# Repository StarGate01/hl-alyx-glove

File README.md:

# Half-Life: Alyx Gravity Glove Replica
Firmware, Hardware and Models for a [Half-Life: Alyx](https://store.steampowered.com/app/546560/HalfLife_Alyx/) inspired glove cosplay prop. Based around an ATMega328p / Arduino Uno.

Also check out the [other images](https://github.com/StarGate01/hl-alyx-glove/tree/master/images)!

## Features

 - Detailed replica of the secondary-hand glove
   - Based on in-game 3D models
 - Custom printed circuit board
   - Small and compact due to SMD design
   - Three red LED matrices for hearts
   - Two individually controllable green status LEDs
   - Two orange finger attractor LEDs
   - Blue 128x64 pixel OLED screen for resin count
   - Red check engine LED light 
   - Moveable attractor fingers
 - Uses standard components for power source and control
 - Microcontroller can be easily reprogrammed
 - Cosmetic parts are printable on any standard 3D printer

## State of the Project

<details>
  <summary>PCB Revision 1: Proof of concept - Completed</summary>

  - [x] OLED rendering of resin count and sprite
  - [x] Display animations on 3 LED matrices
  - [x] Drive 2 green status LEDs
  - [x] Drive check engine LED
  - [x] Evaluate barebone IC
  - [x] Evaluate display drivers
  - [x] Manufacture board
  - [x] Validate board

</details>
 
<details>
  <summary>PCB Revision 2: Refinement - Completed</summary>

  - [x] Add buttons
  - [x] Add 0.1uF caps to driver ICs
  - [x] Larger power traces
  - [x] Re-think trace width in general
  - [x] Properly lay out mounting holes
  - [x] Optimize VCC trace
  - [x] Move OLED connector
  - [x] Optimize board size
  - [x] Think about inertial measurement unit
  - [x] Drive decorative yellow LEDs
  - [x] Improve ground plane stitching
  - [x] Add source info to silkscreen
  - [x] Add component orientation to  silkscreen
  - [x] Evaluate acceleration sensor
  - [x] Manufacture board
  - [x] Validate board

</details>

<details>
  <summary>Firmware Revision 1: Tests - Completed</summary>

  - [x] Test sensor
  - [x] Display resin count
  - [x] Display blinking hearts
  - [x] Flash LEDs
  - [x] Read buttons

</details>

<details>
  <summary>Firmware Revision 2: Demo mode - Completed</summary>

  - [x] State management w/ buttons
  - [x] LED control
  - [x] Adjustable amount of hearts and resin

</details>

<details>
  <summary>Firmware Revision 3: Proper functionality - In Progress</summary>

  - [ ] Wrist flick detection

</details>

<details>
  <summary>Power System - Completed</summary>

  - [x] Battery selection
  - [x] Charging management
  - [x] Verify power system

</details>

<details>
  <summary>CAD and 3D-Printing - Completed</summary>

  - [x] Acquire gloves
  - [x] Export models from game
  - [x] Design decorative parts
  - [x] Adapt decorative parts to 3D-Printing
  - [x] Think about paint and mounting
  - [x] Design battery holder
  - [x] Design PCB mount
  - [x] Mount to glove

</details>

<details>
  <summary>Final Assembly - Completed</summary>

  - [x] Proper paintjob
  - [x] Paint copper elements and add wires
  - [x] LED mounting

</details>

## Software

Clone this repository using `git clone` and open it up in the [PlatformIO IDE](https://platformio.org/).

Edit `include/hardware_config.h` if your pin layout differs.

Finally, use PlatformIO to compile and upload the program. A debug configuration for the Arduino Uno (`uno`) and a release configuration for the PCB (`barebone`) are available. To program the barebone chip, you need a ISP programmer such as a AVRISP, USBasp or Arduino as ISP.

### Compiling Modified Sprites

Use GIMP to export the `xcf` image files into `xdm` files. Make sure to declare the buffers as `PROGMEM`.

### Compiling Modified Fonts

Use a tool like `bdfedit` to view or edit the font.

Install `bdfresize` from your package manager.

Clone [olikraus/u8g2](https://github.com/olikraus/u8g2) and change into the `tools/font/bdfconv` directory. Run `make` and copy or link the `bdfconv` executable to somewhere you can run it.

Change into the `res` directory of this repository. Then run `./font.sh` to pre-compile the font.

## Software Components

 - Arduino
   - [Arduino Framework](https://www.arduino.cc/)
 - 8x8 mini 1.9mm LED matrix with MAX7219 IC using software SPI
   - [wayoda/LedControl](https://platformio.org/lib/show/914/LedControl)
 - 128x64 1.3 inch OLED using hardware I2C
   - [olikraus/U8g2](https://platformio.org/lib/show/942/U8g2)
 - GY-61 ADXL335 Breakout
   - Analog input

## Electronics

Most parts are pretty standard, eg. THT resistors, capacitors and LEDs. Pretty much any electronics store should carry them.

The main controller is a ATMega328p, the same as the Arduino Uno uses. These ICs are cheap for what they offer and also available pretty much everywhere.

The 1.9mm LED matrices are a special part, because they are the "mini" version of the much more widely used 3.0mm/3.75mm 8x8 LED matrices. I bought them from [AliExpress](https://de.aliexpress.com/item/4000931195417.html). The OLED is a fairly standard "Arduino-type" breakout board, and commonly available in blue, yellow and white. [Amazon](https://www.amazon.com/gp/product/B07D9G11DZ) carries them, and so does [AliExpress](https://de.aliexpress.com/item/1005001355009919.html). 

The surface mount LED is a 5050 SMT LED, which is also commonly used in LED strips and can be found at many stores, for example at [Ebay](https://www.ebay.com/itm/LED-Light-SMD-SMT-0603-0805-1206-7030-3020-5730-5050-3528-335-Super-bright/302940504403).

The display drivers are MAX7219CWG ICs, available at many stores, for example [Ebay](https://www.ebay.com/itm/10-St%C3%BCcke-Maxim-MAX7219CWG-SOP-24-Led-Display-Driver-New-Ic-ln/332191432560). However, prices differ a lot depending on the retailer.

The Acceleration sensor is an ADXL335 IC on the GY-61 "Arduino-type" breakout PCB. These modules are so cheap that it is not worth the trouble of including components that can't be hand-soldered. These modules are available at Amazon/Ebay and other retailers.

The power system consists of a 3.7V LiPo Battery commonly used for drones and RC toys (available from e.g. [Ebay](https://www.ebay.com/itm/151372678869)), and an integrated charger/converter board, which is for example available at [Amazon](https://www.amazon.de/gp/product/B07QHTK791). For interfacing, a micro USB socket is used.

### Fabricating the PCB

A [KiCad](https://kicad.org/) project is available in the `hardware` directory. It requires my [custom components](https://github.com/StarGate01/KiCadLibs).

Fabricate the PCB according to the Gerber files in `hardware/gerber` or send them to a factory. I had mine produced by [JLCPCB](https://jlcpcb.com/). All SMD components are hand-solderable using a fine tip and a steady hand.

Solder the components to the PCB according to the KiCAD schematics. Pay extra attention to the orientation of the LED displays and the display drivers ICs, check the little circle markers on the PCB. Sometimes the orientation of the LED matrices is not obvious, so just put them into the holes without soldering and tilt them to jam them, in order to make electrical contact. Then you can verify the orientation if they display correctly.

The mounting holes of the PCB and the OLED module should be on top of each other, such that the modules can be screwed together using an M3 bolt. The acceleration module can be soldered onto the PCB.

## Putting the Glove Together

The actual gloves are called "Half-Jab" by the company Highway 21. Available at motorcycle shops or Amazon/Ebay.

The directory `models` contains STL files for 3D printing. Please note that quite a lot of manual finishing is required depending on your printer. Print all the files in black plastic (I used PLA). The parts are not plug-and-play, you have to sand, cut and drill at various places. Use the parts as a starting point for your own creativity.

Refer to the photos to see how I assembled my version. I used silver metallic automotive sparypaint to color the base piece, and special copper colored paint to paint the copper elements. The rest was painted using acrylic colors.

The attractor LEDs are standard orange LEDs that were inserted into the tips of the finger pieces from above. Their power cables have been routed through a hole in the plastic and back to the PCB.

The "Check engine light" is a 3D printed frame with a piece of printed overhead foil. The frame then gets half-filled with semi-transparent hot glue to create a light diffusor. Print the document `models/check_engine.pdf` on overhead projection foil using a laser/toner printer and cut out one image to size. Insert the foil piece into the frame from the back, such that it rests on the small lip. Make sure the toner side faces inwards, such that it is not exposed to the outside. Then pour in some epoxy or hot glue, but make sure to not fill it up completely. Then position the lamp cover on the PCB where the frame is printed on. I attached it with some small drops of hot glue.

I used various M3 bolts and nuts, and some epoxy glue for the rest of the assembly. The whole assembly is attached to the glove without modifying the glove, instead relying on the two plastic hooks. Use some white zip-ties and some black spiral cable wrap to complete the look.

## Using the PCB

Press the button `SW1` to cycle through the effects, and `SW2` to change / cycle the selected effect. The selection order is: LED hearts amount (initial state) - Green status LED D1 - Green status LED D2 - Red "Check engine" LED D3 - Orange attractor LEDs L1 and L2 - LCD resin count.

## Licensing

All files in this repository are released under the terms of the MIT license. However the original idea and in-game design of the Half-Life: Alyx Glove was made by Valve Software. The copyright of the in-game design is of course held by Valve Software. The files in this repository however are a derivative / transformative work made by the author, and their copyright remains with the author.

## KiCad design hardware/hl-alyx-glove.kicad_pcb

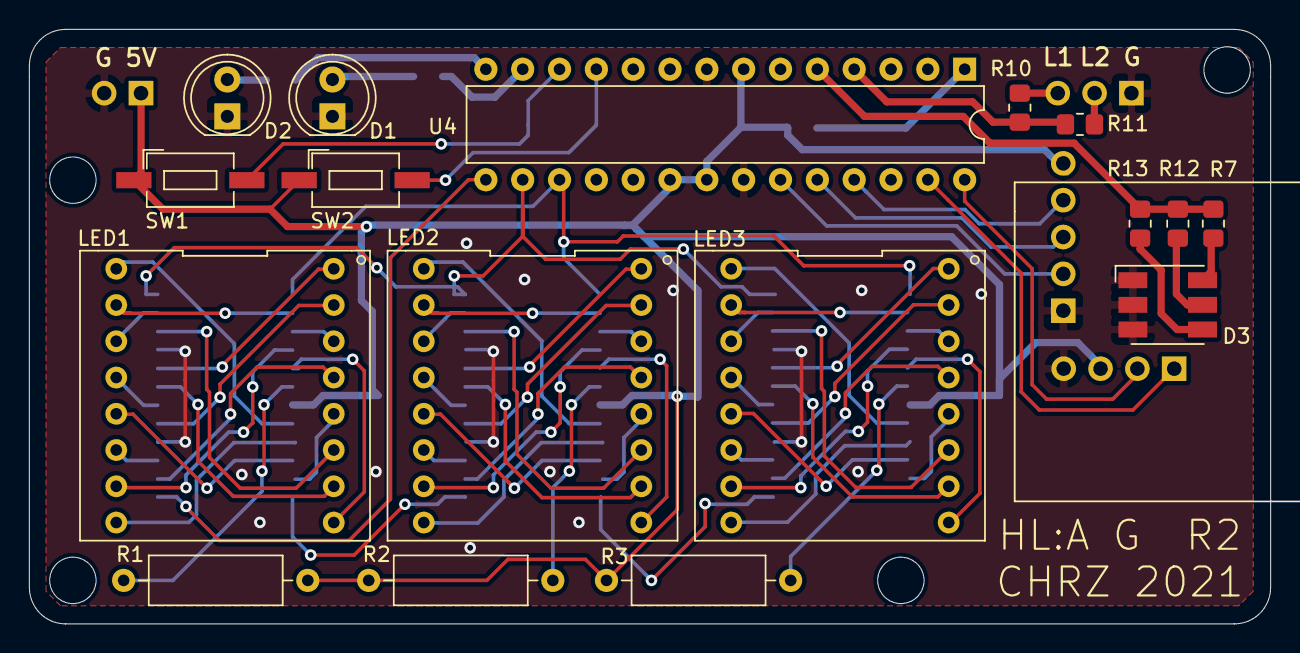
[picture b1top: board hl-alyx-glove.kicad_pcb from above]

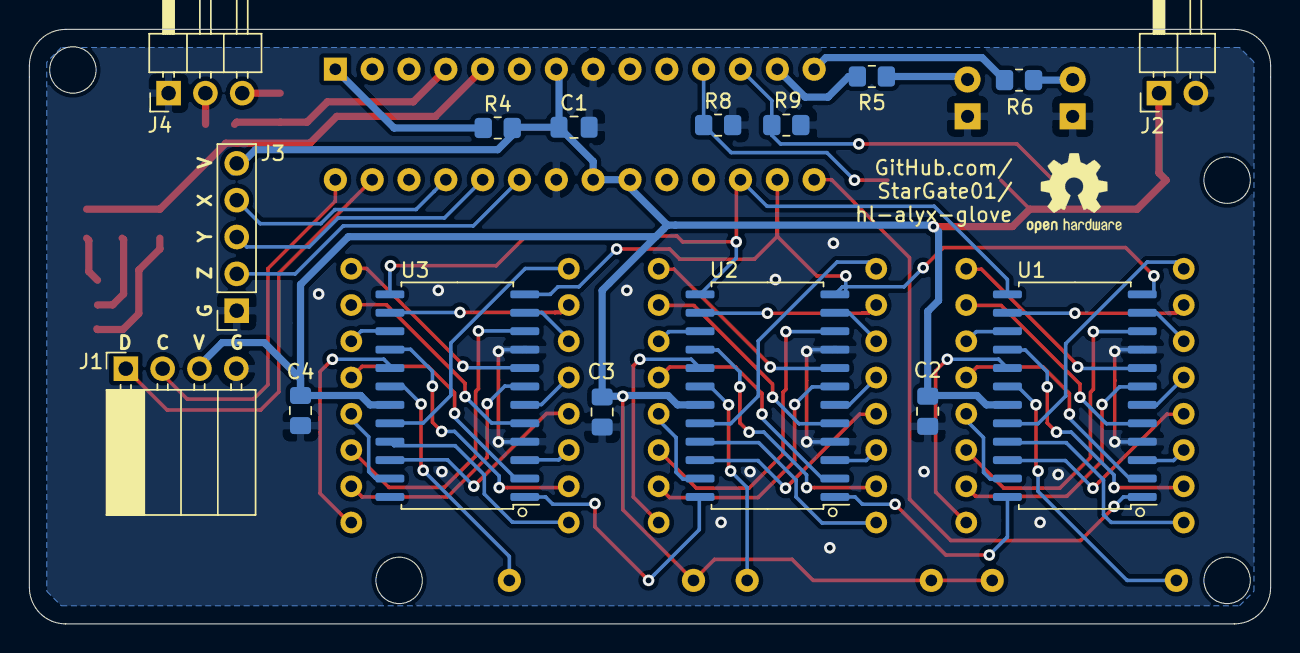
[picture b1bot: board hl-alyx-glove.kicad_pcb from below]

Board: 2 copper layers, 85.6 x 41.0 mm, 37 parts (16 on the bottom side), 77 nets.

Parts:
C1, C2, C3, C4: 100N; C_0805_2012Metric_Pad1.18x1.45mm_HandSolder
D1, D2: GREEN; LED_D5.0mm
D3: RED; LED_RGB_5050-6
H1, H2, H3, H4: MountingHole; MountingHole_3.2mm_M3_DIN965
J1: OLED; PinSocket_1x04_P2.54mm_Horizontal
J2: POWER; PinHeader_1x02_P2.54mm_Horizontal
J3: IMU; PinSocket_1x05_P2.54mm_Vertical
J4: EXT_LED; PinHeader_1x03_P2.54mm_Horizontal
LED1, LED2, LED3: 788BS
R1, R2, R3: 10K; R_Axial_DIN0309_L9.0mm_D3.2mm_P12.70mm_Horizontal
R4, R8, R9: 10K; R_0805_2012Metric_Pad1.20x1.40mm_HandSolder
R5, R6, R7, R10, R11, R12, R13: 180; R_0805_2012Metric_Pad1.20x1.40mm_HandSolder
SW1, SW2: SW_Push; smd_switch_sunrom4388
U1, U2, U3: MAX7219; SOP-24_7.5x15.4mm_P1.27mm
U4: ATmega328P-PU; DIP-28_W7.62mm

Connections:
/LED_Matrix_0/C1: LED1.5, U1.22
/LED_Matrix_0/C2: LED1.2, U1.14
/LED_Matrix_0/C3: LED1.7, U1.16
/LED_Matrix_0/C4: LED1.1, U1.20
/LED_Matrix_0/C5: LED1.12, U1.23
/LED_Matrix_0/C6: LED1.8, U1.21
/LED_Matrix_0/C7: LED1.14, U1.15
/LED_Matrix_0/C8: LED1.9, U1.17
/LED_Matrix_0/CLK: U1.13, U2.13, U3.13, U4.17
/LED_Matrix_0/DIN: U1.1, U4.15
/LED_Matrix_0/LOAD: U1.12, U2.12, U3.12, U4.16
/LED_Matrix_0/R1: LED1.13, U1.2
/LED_Matrix_0/R2: LED1.3, U1.11
/LED_Matrix_0/R3: LED1.4, U1.6
/LED_Matrix_0/R4: LED1.10, U1.7
/LED_Matrix_0/R5: LED1.6, U1.3
/LED_Matrix_0/R6: LED1.11, U1.10
/LED_Matrix_0/R7: LED1.15, U1.5
/LED_Matrix_0/R8: LED1.16, U1.8
/LED_Matrix_1/C1: LED2.5, U2.22
/LED_Matrix_1/C2: LED2.2, U2.14
/LED_Matrix_1/C3: LED2.7, U2.16
/LED_Matrix_1/C4: LED2.1, U2.20
/LED_Matrix_1/C5: LED2.12, U2.23
/LED_Matrix_1/C6: LED2.8, U2.21
/LED_Matrix_1/C7: LED2.14, U2.15
/LED_Matrix_1/C8: LED2.9, U2.17
/LED_Matrix_1/DIN: U1.24, U2.1
/LED_Matrix_1/R1: LED2.13, U2.2
/LED_Matrix_1/R2: LED2.3, U2.11
/LED_Matrix_1/R3: LED2.4, U2.6
/LED_Matrix_1/R4: LED2.10, U2.7
/LED_Matrix_1/R5: LED2.6, U2.3
/LED_Matrix_1/R6: LED2.11, U2.10
/LED_Matrix_1/R7: LED2.15, U2.5
/LED_Matrix_1/R8: LED2.16, U2.8
/LED_Matrix_2/C1: LED3.5, U3.22
/LED_Matrix_2/C2: LED3.2, U3.14
/LED_Matrix_2/C3: LED3.7, U3.16
/LED_Matrix_2/C4: LED3.1, U3.20
/LED_Matrix_2/C5: LED3.12, U3.23
/LED_Matrix_2/C6: LED3.8, U3.21
/LED_Matrix_2/C7: LED3.14, U3.15
/LED_Matrix_2/C8: LED3.9, U3.17
/LED_Matrix_2/DIN: U2.24, U3.1
/LED_Matrix_2/R1: LED3.13, U3.2
/LED_Matrix_2/R2: LED3.3, U3.11
/LED_Matrix_2/R3: LED3.4, U3.6
/LED_Matrix_2/R4: LED3.10, U3.7
/LED_Matrix_2/R5: LED3.6, U3.3
/LED_Matrix_2/R6: LED3.11, U3.10
/LED_Matrix_2/R7: LED3.15, U3.5
/LED_Matrix_2/R8: LED3.16, U3.8
GND: C1.2, C2.2, C3.2, C4.2, D1.1, D2.1, D3.1, D3.2, D3.3, J1.4, J2.2, J3.1, J4.1, R8.1, R9.1, U1.4, U1.9, U2.4, U2.9, U3.4, U3.9, U4.8, U4.22
unnamed: D1.2, R5.1
unnamed: D2.2, R6.1
unnamed: D3.4, R13.1
unnamed: D3.5, R12.1
unnamed: D3.6, R7.1
unnamed: J1.1, U4.27
unnamed: J1.2, U4.28
unnamed: J3.2, U4.23
unnamed: J3.3, U4.24
unnamed: J3.4, U4.25
unnamed: J4.2, R11.1
unnamed: J4.3, R10.1
unnamed: R1.1, U1.18
unnamed: R2.1, U2.18
unnamed: R3.1, U3.18
unnamed: R4.2, U4.1
unnamed: R5.2, U4.13
unnamed: R6.2, U4.14
unnamed: R8.2, SW2.2, U4.11
unnamed: R9.2, SW1.2, U4.12
unnamed: R10.2, R11.2, U4.4
unnamed: R7.2, R12.2, R13.2, U4.5
VCC: C1.1, C2.1, C3.1, C4.1, J1.3, J2.1, J3.5, R1.2, R2.2, R3.2, R4.1, SW1.1, SW2.1, U1.19, U2.19, U3.19, U4.7, U4.20, U4.21

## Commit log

2021-01-17 First tests
2021-01-17 font test
2021-01-17 Update font and readme
2021-01-17 Add resin text
2021-01-17 Add hardware
2021-01-17 schematic first version
2021-01-17 add some missing components
2021-01-19 pcb first version
2021-01-19 Add rev 1 gerber files
2021-01-27 Add barebone config, leds & resistor values
2021-02-01 small fix for barebone
2021-02-01 add image
2021-02-04 PCB rev 2 first changes
2021-02-04 add second led
2021-02-04 add missing resistors to big led
2021-02-04 small fixes
2021-02-04 kicad save
2021-02-04 fix button footprints
2021-02-04 small fix
2021-02-04 Implement sensors
2021-02-04 Add rev 2 gerber files
2021-02-05 update progress
2021-02-16 Completed hardware tests for PCV r2
2021-03-14 Add models
2021-03-23 Add rest of models
2021-03-23 add bumper models
2021-03-23 first version done
2021-03-24 Begin demo
2021-03-24 Finish demo mode
2021-03-24 add images
2021-09-27 Clarify a few things
